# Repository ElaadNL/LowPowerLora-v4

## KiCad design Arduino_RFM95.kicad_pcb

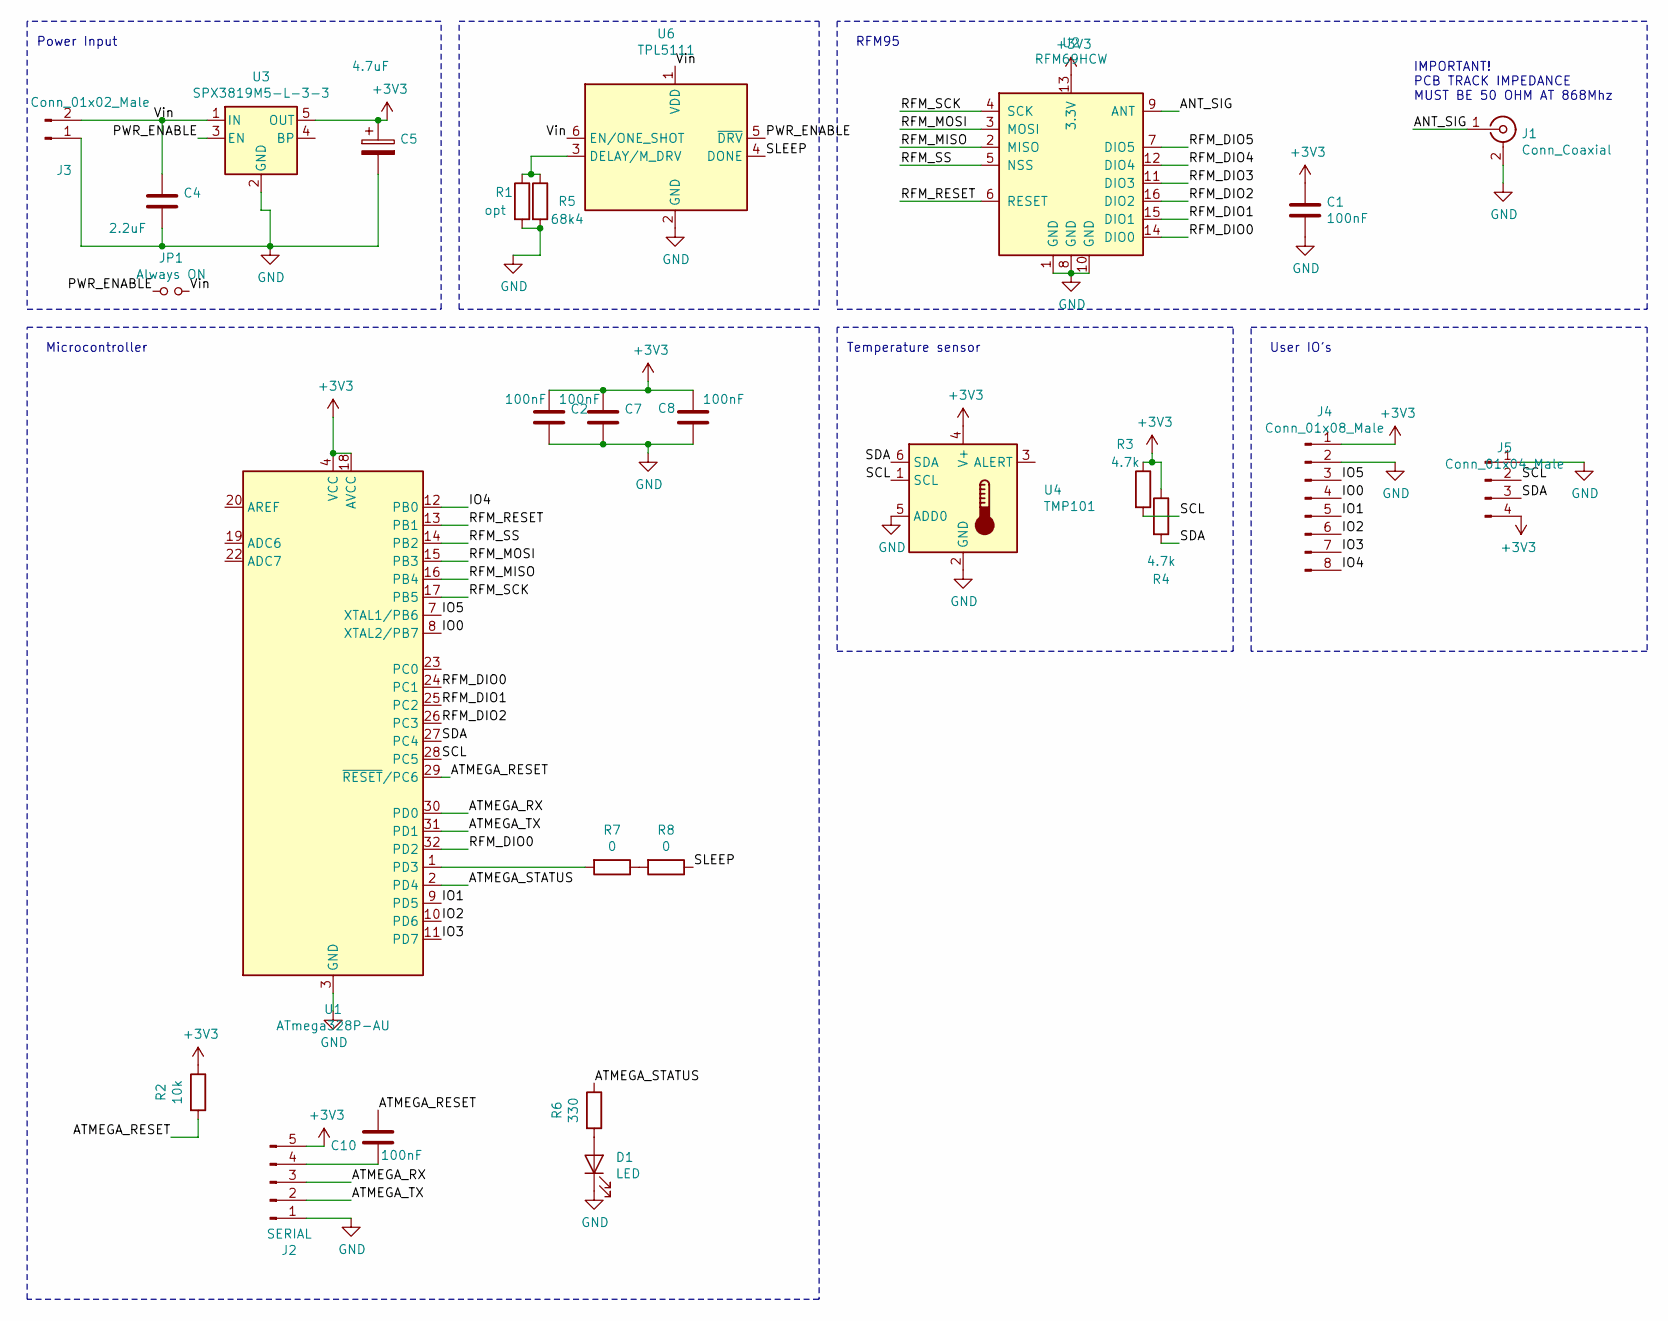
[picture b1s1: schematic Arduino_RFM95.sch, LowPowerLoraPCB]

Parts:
C1, C2, C7, C8, C10: 100nF; C_0805_2012Metric
C4: 2.2uF; C_0805_2012Metric
C5: 4.7uF; C_0805_2012Metric
D1: LED; LED_0805_2012Metric
J1: Conn_Coaxial; U.FL_Hirose_U.FL-R-SMT-1_Vertical
J2: SERIAL; PinHeader_1x05_P2.54mm_Horizontal
J3: Conn_01x02_Male; PinHeader_1x02_P2.54mm_Horizontal
J4: Conn_01x08_Male; PinHeader_1x08_P2.54mm_Vertical
J5: Conn_01x04_Male; PinHeader_1x04_P2.54mm_Vertical
JP1: Always ON; SolderJumper-2_P1.3mm_Open_RoundedPad1.0x1.5mm
R1: opt; R_0805_2012Metric
R2: 10k; R_0805_2012Metric
R3, R4: 4.7k; R_0805_2012Metric
R5: 68k4; R_0805_2012Metric
R6: 330; R_0805_2012Metric
R7: 0; R_1206_3216Metric
R8: 0; R_0805_2012Metric
U1: ATmega328P-AU; TQFP-32_7x7mm_P0.8mm
U2: RFM69HCW; HOPERF_RFM9XW_SMD
U3: SPX3819M5-L-3-3; SOT-23-5
U4: TMP101; SOT-23-6
U6: TPL5111; SOT-23-6

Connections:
+3V3: C1.2, C2.2, C5.1, C7.2, C8.2, J2.5, J4.1, J5.4, R2.1, R3.1, R4.1, U1.4 (VCC), U1.6 (VCC), U1.18 (AVCC), U2.13 (3.3V), U3.5 (OUT), U4.4 (V+)
/ANT_SIG: J1.1 (In), U2.9 (ANT)
/ATMEGA_RESET: C10.1, R2.2, U1.29 (~RESET~/PC6)
/ATMEGA_RX: J2.3, U1.30 (PD0)
/ATMEGA_STATUS: R6.1, U1.2 (PD4)
/ATMEGA_TX: J2.2, U1.31 (PD1)
/IO0: J4.4, U1.8 (XTAL2/PB7)
/IO1: J4.5, U1.9 (PD5)
/IO2: J4.6, U1.10 (PD6)
/IO3: J4.7, U1.11 (PD7)
/IO4: J4.8, U1.12 (PB0)
/IO5: J4.3, U1.7 (XTAL1/PB6)
/PWR_ENABLE: JP1.1, U3.3 (EN), U6.5 (~DRV)
/RFM_DIO0: U1.24 (PC1), U1.32 (PD2), U2.14 (DIO0)
/RFM_DIO1: U1.25 (PC2), U2.15 (DIO1)
/RFM_DIO2: U1.26 (PC3), U2.16 (DIO2)
/RFM_DIO3: U2.11 (DIO3)
/RFM_DIO4: U2.12 (DIO4)
/RFM_DIO5: U2.7 (DIO5)
/RFM_MISO: U1.16 (PB4), U2.2 (MISO)
/RFM_MOSI: U1.15 (PB3), U2.3 (MOSI)
/RFM_RESET: U1.13 (PB1), U2.6 (RESET)
/RFM_SCK: U1.17 (PB5), U2.4 (SCK)
/RFM_SS: U1.14 (PB2), U2.5 (NSS)
/SCL: J5.2, R3.2, U1.28 (PC5), U4.1 (SCL)
/SDA: J5.3, R4.2, U1.27 (PC4), U4.6 (SDA)
/SLEEP: R8.1, U6.4 (DONE)
/Vin: C4.2, J3.2, JP1.2, U3.1 (IN), U6.1 (VDD), U6.6 (EN/ONE_SHOT)
GND: C1.1, C2.1, C4.1, C5.2, C7.1, C8.1, D1.1 (K), J1.2 (Ext), J2.1, J3.1, J4.2, J5.1, R1.2, R5.2, U1.3 (GND), U1.5 (GND), U1.21 (GND), U2.1 (GND), U2.8 (GND), U2.10 (GND), U3.2 (GND), U4.2 (GND), U4.5 (ADD0), U6.2 (GND)
unnamed: C10.2, J2.4
unnamed: D1.2 (A), R6.2
unnamed: R1.1, R5.1, U6.3 (DELAY/M_DRV)
unnamed: R7.1, R8.2
unnamed: R7.2, U1.1 (PD3)

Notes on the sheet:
Power Input
RFM95
IMPORTANT! PCB TRACK IMPEDANCE MUST BE 50 OHM AT 868Mhz
Microcontroller
Temperature sensor
User IO’s

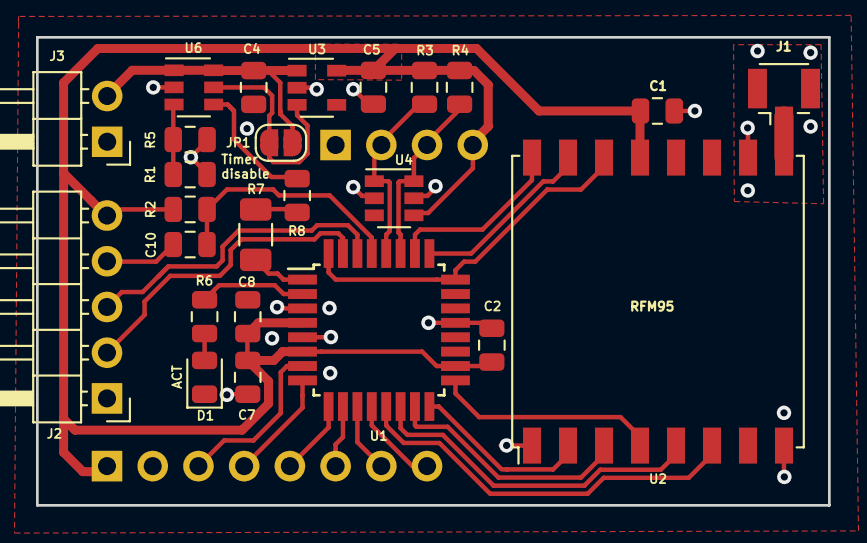
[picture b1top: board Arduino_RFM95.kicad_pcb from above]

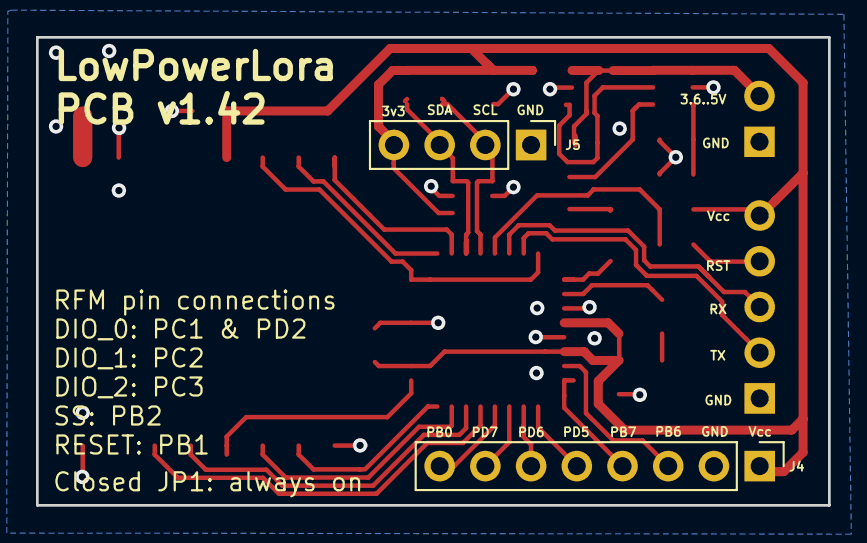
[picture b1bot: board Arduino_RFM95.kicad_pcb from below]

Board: 2 copper layers, 44.0 x 26.0 mm, 27 parts (2 on the bottom side), 31 nets.
